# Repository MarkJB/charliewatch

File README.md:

Charliewatch
---

An "Analog" watch with 72 (60+12) Charlieplexed LEDs. Based on Travis Goodspeed's
GoodWatch21 schematic, using the CC430F5137IRGZR CPU, which doesn't have the LCD
controller of the CC430F6xxx in the GoodWatch.

v0.2 works, although it has no radio parts.  It is exactly 1 square inch
of PCB and should fit in a 38mm or 36mm case.

See it in action: https://www.youtube.com/watch?v=VaebR-6KNXE

[Charliewtch schematic](datasheets/charliewatch.pdf)

Bill Of Materials (BOM)
---
- CC430F5137IRGZR [https://www.mouser.co.uk/ProductDetail/595-CC430F5137IRGZR](https://www.mouser.co.uk/ProductDetail/595-CC430F5137IRGZR)

- 0603 68k Resistor [ERA3AEB683V](https://uk.farnell.com/panasonic/era3aeb683v/res-68k-0-1-0-1w-0603-thin-film/dp/1577630)

- 0603 Red LED [KP-1608EC](https://uk.farnell.com/kingbright/kp-1608ec/led-red-8mcd-625nm-smd/dp/2463988)

- KEYSTONE  3002  Battery Contact, Coin Cell - 20mm, SMD [3002](https://uk.farnell.com/keystone/3002/battery-smd-retainer-20mm/dp/1650693)

- IQD FREQUENCY PRODUCTS  LFXTAL050789  Crystal, 32.768 kHz, SMD, 2mm x 1.2mm, 12.5 pF, 20 ppm, IQXC-25 Series [LFXTAL050789](https://uk.farnell.com/iqd-frequency-products/lfxtal050789/crystal-32-768khz-12-5pf-smd/dp/2449502)

- Push button - Omron [B3U3100P](https://uk.farnell.com/omron/b3u-3000p/tactile-switch-side-actuated-smd/dp/1333655)

Programming
---

Programmed via TI Code Composer Studio using the Programmer/Debugger on the MSP430 FR4133 Launchpad.
http://www.ti.com/tool/MSP-EXP430FR4133

Programming cable
---

From the top of the board: (Wiring from watch to Programmer/Debugger on MSP430 FR4133 Launchpad) 
* TST - SBWTCK
* RST - SBWTDIO
* RX - RXD
* TX - TXD
* VCC - 3V3
* GND - GND

There is also a four-wire setup that might simplify the wiring.
Travis documents it and the power consumption here:
https://github.com/travisgoodspeed/goodwatch/wiki/EnergyTrace

Bricked Launchpad
-----

If you brick your launchpad by running Energia under Linux, it will no
longer program the Charliewatch.  The other weirdness is that `tilib`
can detect the device, but can't write to it unless run as root.

Energy Trace
----
* `libmsp430.so`: https://dlbeer.co.nz/articles/slac460y/index.html
* https://github.com/carrotIndustries/energytrace-util
* Have to update path to `MSP430.h` from the `slac/DLL430_v3/include` directory

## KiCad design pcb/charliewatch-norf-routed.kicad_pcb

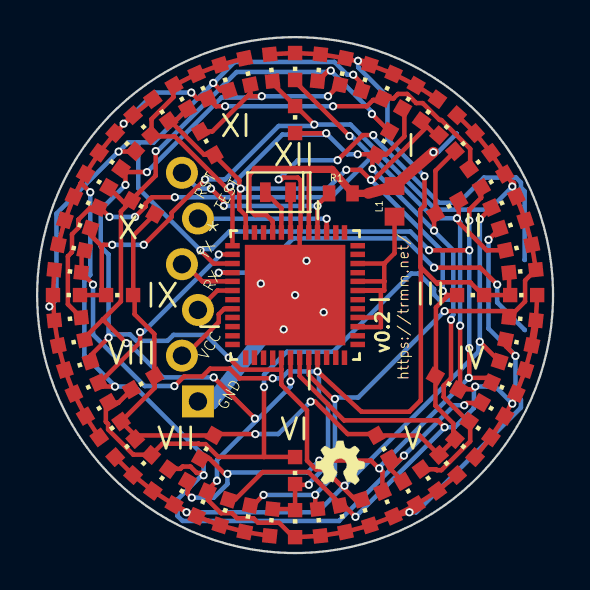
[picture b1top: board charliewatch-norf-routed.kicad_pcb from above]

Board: 2 copper layers, 28.7 x 28.7 mm, 85 parts (0 on the bottom side), 20 nets.

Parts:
JP1: 1X06-BIGLOCK
L1: R0603
LED0, LED1, LED2, LED3, LED4, LED5, LED6, LED7, LED8, LED9, LED10, LED11, LED12, LED13, LED14, LED15, LED16, LED17, LED18, LED19, LED20, LED21, LED22, LED23, LED24, LED25, LED26, LED27, LED28, LED29, LED30, LED31, LED32, LED33, LED34, LED35, LED36, LED37, LED38, LED39, LED40, LED41, LED42, LED43, LED44, LED45, LED46, LED47, LED48, LED49, LED50, LED51, LED52, LED53, LED54, LED55, LED56, LED57, LED58, LED59, LED60, LED61, LED62, LED63, LED64, LED65, LED66, LED67, LED68, LED69, LED70, LED71: CHIPLED_0603
R1: 75k; R0402
S2: MOMENTARY-SWITCH-SPST-SMD-RIGHT-ANGLE; TACTILE_SWITCH_SMD_RIGHT_ANGLE
TP1: PTR1TP10SQ; TP10SQ
TP2, TP3, TP4, TP5, TP6: PTR1TP10R; TP10R
U2: CC430F5137IRGZR; QFN50P700X700X100-49N
U$1: CR2032-SMD
X1: CRYSTALS-NOGND-IQXC-25; 2.0X1.2-2PAD

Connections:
AVCC: L1.1, U2.27, U2.28, U2.31, U2.32, U2.34
B0: LED0.A, LED1.A, LED2.A, LED3.A, LED4.A, LED5.A, LED6.A, LED7.A, LED8.C, LED16.C, LED24.C, LED32.C, LED40.C, LED48.C, LED56.C, LED64.C, U2.21
B1: LED0.C, LED8.A, LED9.A, LED10.A, LED11.A, LED12.A, LED13.A, LED14.A, LED15.A, LED17.C, LED25.C, LED33.C, LED41.C, LED49.C, LED57.C, LED65.C, U2.20
B2: LED1.C, LED9.C, LED16.A, LED17.A, LED18.A, LED19.A, LED20.A, LED21.A, LED22.A, LED23.A, LED26.C, LED34.C, LED42.C, LED50.C, LED58.C, LED66.C, U2.19
B3: LED2.C, LED10.C, LED18.C, LED24.A, LED25.A, LED26.A, LED27.A, LED28.A, LED29.A, LED30.A, LED31.A, LED35.C, LED43.C, LED51.C, LED59.C, LED67.C, U2.18
B4: LED3.C, LED11.C, LED19.C, LED27.C, LED32.A, LED33.A, LED34.A, LED35.A, LED36.A, LED37.A, LED38.A, LED39.A, LED44.C, LED52.C, LED60.C, LED68.C, U2.17
B5: LED4.C, LED12.C, LED20.C, LED28.C, LED36.C, LED40.A, LED41.A, LED42.A, LED43.A, LED44.A, LED45.A, LED46.A, LED47.A, LED53.C, LED61.C, LED69.C, U2.3
B6: LED5.C, LED13.C, LED21.C, LED29.C, LED37.C, LED45.C, LED48.A, LED49.A, LED50.A, LED51.A, LED52.A, LED53.A, LED54.A, LED55.A, LED62.C, LED70.C, U2.2
B7: LED6.C, LED14.C, LED22.C, LED30.C, LED38.C, LED46.C, LED54.C, LED56.A, LED57.A, LED58.A, LED59.A, LED60.A, LED61.A, LED62.A, LED63.A, LED71.C, U2.1
B8: LED7.C, LED15.C, LED23.C, LED31.C, LED39.C, LED47.C, LED55.C, LED63.C, LED64.A, LED65.A, LED66.A, LED67.A, LED68.A, LED69.A, LED70.A, LED71.A, U2.48
BSL_RST: JP1.6, R1.1, TP6.TP, U2.40
BSL_RX: JP1.3, TP3.TP, U2.6
BSL_TEST: JP1.5, TP5.TP, U2.39
BSL_TX: JP1.4, TP4.TP, U2.5
BSL_VCC: JP1.2, TP2.TP, U2.8
BUTTON: S2.2, U2.4
GND: JP1.1, S2.1, TP1.TP, U2.42, U2.49, U$1.-
VCC: L1.2, R1.2, U2.41, U2.45, U$1.+$1
XIN: U2.44, X1.2
XOUT: U2.43, X1.1

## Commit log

2019-09-23 Imported PCB to kicad and modified the silkscreen to be Roman Numerals, included zip of gerber files.
2020-01-05 Use compile time vars with CCS on Windows
    Added makefile.defs to create and add the BUILDTIME and BUILDSEC vars to the TI Code Composer Studio managed makefile.
2020-01-08 Update README.md
    Added details of programmer used and connections. Removed references to v0.1.
2020-01-08 Add picture of MakeBmth build
2020-01-13 add case folder and pcb models
    Added a folder for new case models.
    Moved some images into images folder
    Added step & wrl PCB models for case modelling.
2020-01-13 Use 'R12' instead of 'R15'
    Used the assembler workaround for RC3 errata as per http://www.ti.com/lit/er/slaz094aa/slaz094aa.pdf.
    This is TIs code but pulled from Travis Goodspeeds 'Goodwatch' repo as the 'R15' version wasn't working for me reliably in CCS and GCC.
    https://github.com/travisgoodspeed/goodwatch/commit/9eab697c9aca721d29e7ae4a1e4f9f9b0aaded59
2020-01-13 Workaround for XT1 stabilization test
    Disable XT1 stabilization test as this stop the watch starting up on the board I built. Seems to run fine without it. Need to determine if this is detremental to normal operation.
2020-01-13 Add case and stencil puck stls
    Add new case stl.
    Add the PCB stencil jig 'puck'. This is a jig with holes for 2.54mm pins that line up with the programming pin holes in the PCB to make lining up with the solder paste screen easier. This is 18mm thi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
2020-01-14 Add 'leds off' mode
    Added a 'low power' mode where all leds are off until the mode is disabled (short press) and then times out or long press to go back to mode 0 (animation_draw).
2020-01-14 Auto power off leds on main display
    If enabled time display mode will turn off the leds after 60 seconds. Short press to display time again.
